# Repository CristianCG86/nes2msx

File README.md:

# NES2MSX

## Description
Converter for NES controllers (7-pin connector) to MSX standard.

## Acknowledgments
- David A. Mellis for his ATtiny board library (https://github.com/damellis/attiny).
- Josh Marinacci for his NESpad library (https://github.com/joshmarinacci/nespad-arduino).

## Why?
This project was born out of the difficulty of finding comfortable and accessible (and also affordable 🤑) controllers for MSX computers.  
But instead of destroying a NES controller, I decided to make this converter — that way I could also use other NES-style controllers such as those from 8Bitdo.

## Images
### PCB

### Assembled PCB

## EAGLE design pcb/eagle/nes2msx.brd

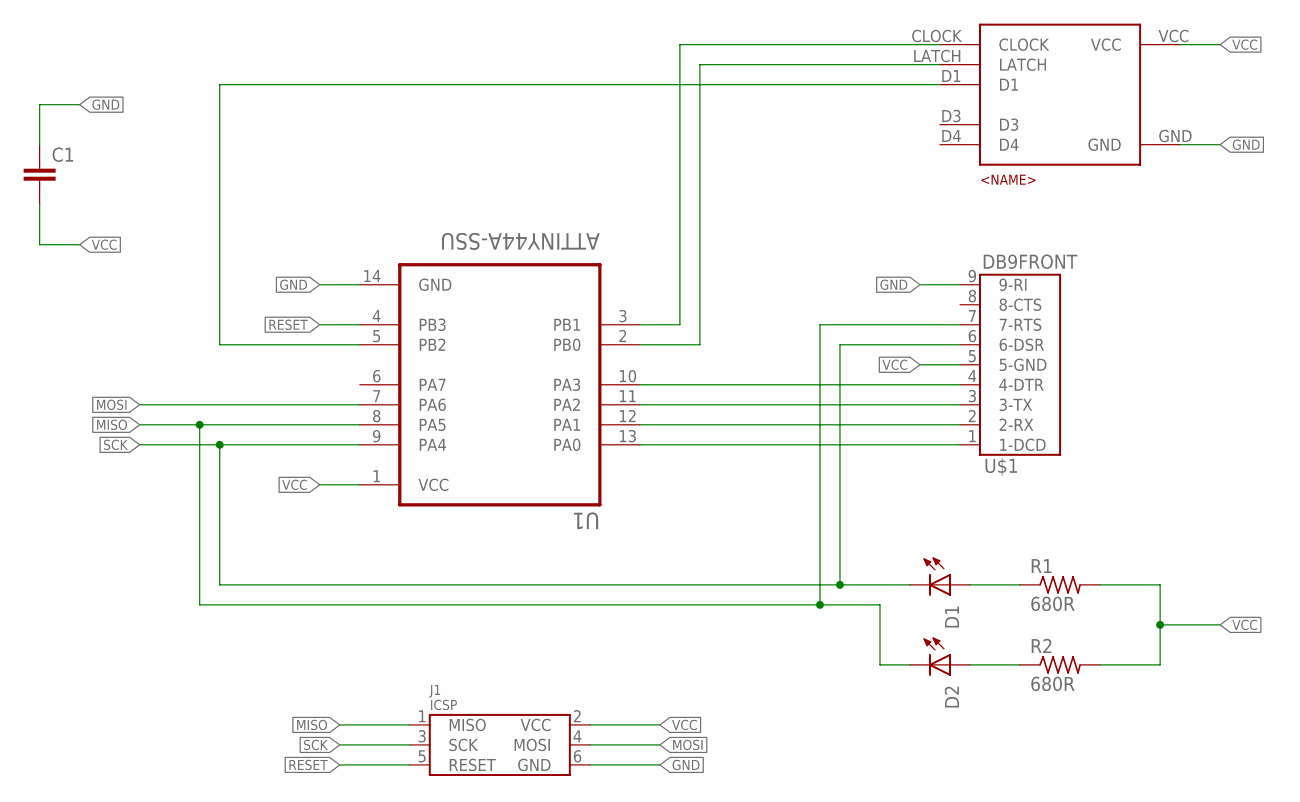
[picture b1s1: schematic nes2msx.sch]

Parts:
C1: C-EUC0805; C0805
D1, D2: LED-0805; 0805-LED
J1: ICSP; M03X2
R1, R2: 680R; R0805
U1: ATTINY44A-SSU; SOIC127P600X175-14N
U$1: DB9FRONT; DB9_FRONT
U$3: NES_CONTROLLERL; NES_CONTROLLER

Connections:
GND: C1.1, J1.6 (GND), U1.14 (GND), U$1.9 (9-RI), U$3.GND
MISO: D2.C, J1.1 (MISO), U1.8 (PA5), U$1.7 (7-RTS)
MOSI: J1.4 (MOSI), U1.7 (PA6)
unnamed: U1.13 (PA0), U$1.1 (1-DCD)
unnamed: U1.12 (PA1), U$1.2 (2-RX)
unnamed: U1.11 (PA2), U$1.3 (3-TX)
unnamed: U1.10 (PA3), U$1.4 (4-DTR)
unnamed: U1.3 (PB1), U$3.CLOCK
unnamed: U1.2 (PB0), U$3.LATCH
unnamed: U1.5 (PB2), U$3.D1
unnamed: D1.A, R1.1
unnamed: D2.A, R2.1
RESET: J1.5 (RESET), U1.4 (PB3)
SCK: D1.C, J1.3 (SCK), U1.9 (PA4), U$1.6 (6-DSR)
VCC: C1.2, J1.2 (VCC), R1.2, R2.2, U1.1 (VCC), U$1.5 (5-GND), U$3.VCC

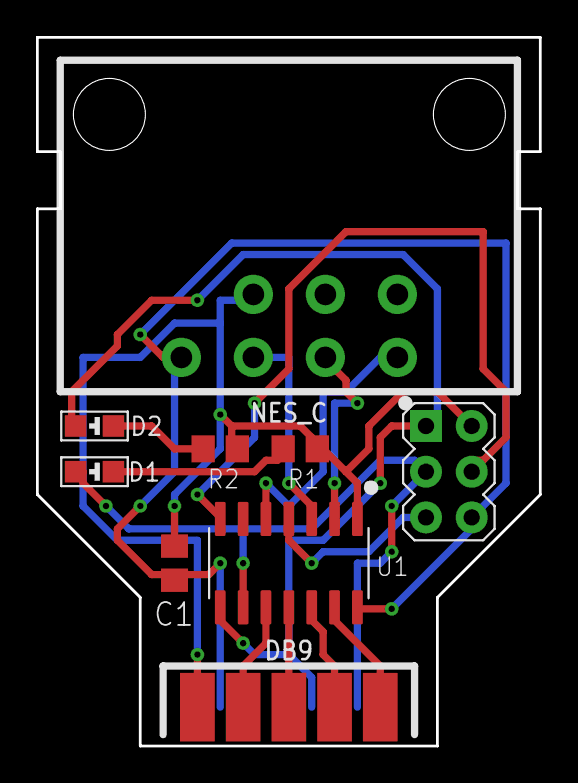
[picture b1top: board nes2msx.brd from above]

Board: 2 copper layers, 27.9 x 39.4 mm, 9 parts (0 on the bottom side), 15 nets.

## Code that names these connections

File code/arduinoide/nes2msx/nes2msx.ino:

#include "nespad.h"

/**
  ---- Prerequisites -------------------------------------------

  ATtiny boards from David A. Mellis
  https://github.com/damellis/attiny


  ---- Arduino IDE configuration -------------------------------

  Boards -> attiny -> ATtiny 24/44/84
  Clock -> Internal 8 MHz
  Processor -> ATtiny 44


  ---- Wire connection -----------------------------------------

  NES controller conection          MSX controller conection                                                        
          ____                           _____________      
         | 1   \                         \ 1 2 3 4 5 /      
         | 2  5 |                         \ 6 7 8 9 /       
         | 3  6 |                           -------         
         | 4  7 |                                           
          ------                      ┌─────┬───────────┐   
                                      │ MSX │   ATtiny  │   
    ┌─────┬───────────┐               ├─────┼───────────┤   
    │ NES │   ATtiny  │               │  1  │  PA0 [13] │   
    ├─────┼───────────┤               │  2  │  PA1 [12] │   
    │  1  │  VCC [1]  │               │  3  │  PA2 [11] │   
    │  2  │  PB1 [3]  │               │  4  │  PA3 [10] │   
    │  3  │  PB0 [2]  │               │  5  │  VCC [1]  │   
    │  4  │  PB2 [5]  │               │  6  │  PA5 [9]  │   
    │  5  │  GND [14] │               │  7  │  PA4 [8]  │   
    │  6  │  NC       │               │  8  │  NC       │   
    │  7  │  NC       │               │  9  │  GND [14] │   
    └─────┴───────────┘               └─────┴───────────┘   
*/

//  Turbo speed config
#define TURBO_INITIAL_SPEED 2
#define TURBO_MAX_SPEED 2
#define TURBO_INCREASE_SPEED 1

//  Turbo variables
uint8_t turbo_select_counter;
uint8_t turbo_select_toggler;
uint8_t turbo_select_pushed;
uint8_t turbo_select_speed;

uint8_t turbo_start_counter;
uint8_t turbo_start_toggler;
uint8_t turbo_start_pushed;
int8_t turbo_start_speed;

//  NES controller reader
NESpad nintendo = NESpad(10, 9, 8);

//  Input buffer
byte state = 0;

//  Output buffer
uint8_t state_processed;

void setup() {
  // Set port B as outputs and set to high
  DDRA = B11111111;
  PORTA = B11111111;

  // Initilization turbo vars
  turbo_select_counter = 0;
  turbo_select_toggler = 0;
  turbo_select_pushed = 0;

  turbo_start_counter = 0;
  turbo_start_toggler = 0;
  turbo_start_pushed = 0;
}

void loop() {
  
  state = nintendo.buttons();

  // Reorder buttons
  state_processed = ((state & (1 << 1)) << 3) |  // B -> bit4
           ((state & (1 << 0)) << 5) |  // A -> bit5
           ((state & (1 << 7)) >> 4) |  // R -> bit3
           ((state & (1 << 6)) >> 4) |  // L -> bit2
           ((state & (1 << 5)) >> 4) |  // D -> bit1
           ((state & (1 << 4)) >> 4);   // U -> bit0

  // Turbo SELECT (B)
  if(state & NES_SELECT) {
    turbo_select_pushed = 1;
  } else if(turbo_select_pushed == 1) {
    run_b_turbo();
    turbo_select_pushed = 0;
  }

  if(turbo_select_toggler == 1 && (turbo_select_counter >> 1) == 0) {
    state_processed = state_processed & 0b11101111;
  }

  // Turbo START (A)
  if(state & NES_START) {
    turbo_start_pushed = 1;
  } else if(turbo_start_pushed == 1) {
    run_a_turbo();
    turbo_start_pushed = 0;
  }

  if(turbo_start_toggler == 1 && (turbo_start_counter >> 1) == 0) {
    state_processed = state_processed & 0b11011111;
  }

  // Put data button into MSX port
  PORTA = ~(state_processed & 0b00111111);

  // Turbo counters
  turbo_select_counter++;
  if(turbo_select_counter > turbo_select_speed) turbo_select_counter = 0;
  
  turbo_start_counter++;
  if(turbo_start_counter > turbo_start_speed) turbo_start_counter = 0;
  
  delay(3);
}

//  Turbo operations (A)
void run_a_turbo() {
  if(turbo_start_toggler == 0) {
    turbo_start_toggler = 1;
    turbo_start_speed = TURBO_INITIAL_SPEED;
  } else if(turbo_start_speed < TURBO_MAX_SPEED) {
    turbo_start_speed += TURBO_INCREASE_SPEED;
  } else {
    turbo_start_toggler = 0;
    turbo_start_speed = 0;
  }
}

//  Turbo operations (B)
void run_b_turbo() {
  if(turbo_select_toggler == 0) {
    turbo_select_toggler = 1;
    turbo_select_speed = TURBO_INITIAL_SPEED;
  } else if(turbo_select_speed < TURBO_MAX_SPEED) {
    turbo_select_speed += TURBO_INCREASE_SPEED;
  } else {
    turbo_select_toggler = 0;
    turbo_select_speed = 0;
  }
}

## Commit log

2025-09-21 First commit of local project nes2msx
2025-09-22 Refactor Gerber files for nes2msx PCB design
2025-10-20 Refactor code structure for improved readability and maintainability
2025-10-20 Added license file
